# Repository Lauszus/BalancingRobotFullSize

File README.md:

# Balancing robot full size
#### Developed by Kristian Sloth Lauszus and Mads Friis Bornebusch, 2014

The code is released under the GNU General Public License.
_________

This is the code for my full size balancing robot.

Both our paper and poster can be found inside the [Documents](Documents) directory.

Detailed information can be found at the blog post: <http://blog.tkjelectronics.dk/2014/07/full-size-diy-balancing-robot/>.

## Android application

I have also written an Android application for the robot. The source code is available at the following link: <https://github.com/Lauszus/BalancingRobotFullSizeAndroid>.

For more information send me an email at <lauszus@gmail.com>.

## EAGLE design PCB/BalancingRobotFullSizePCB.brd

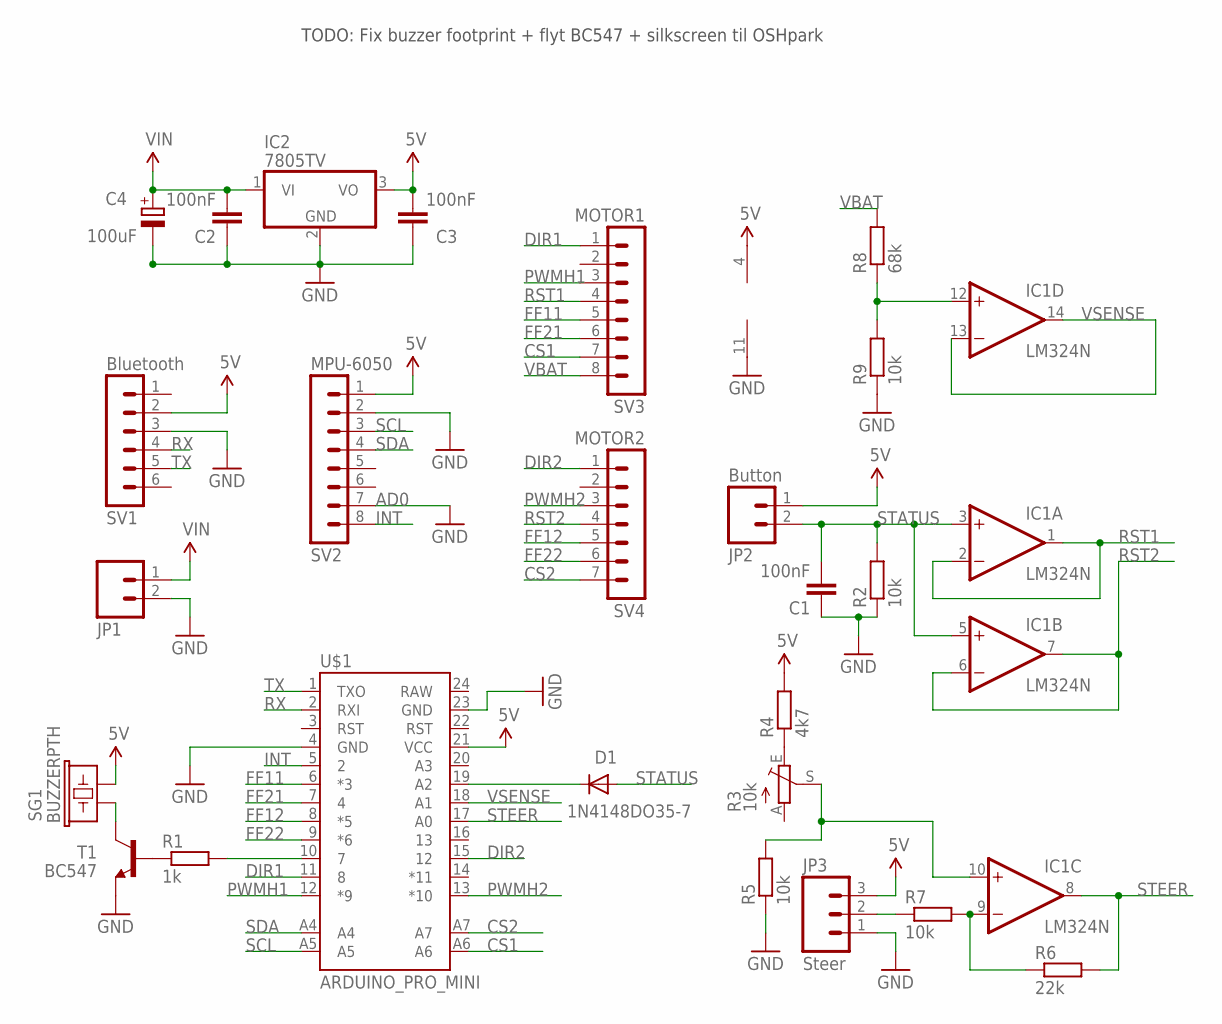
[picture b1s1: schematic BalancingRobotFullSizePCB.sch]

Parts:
C1, C2, C3: 100nF; C025-025X050
C4: 100uF; E2,5-5
D1: 1N4148DO35-7; DO35-7
IC1: LM324N; DIL14
IC2: 7805TV; TO220V
JP1: M02PTH; 1X02
JP2: Button; 1X02
JP3: Steer; 1X03
R1: 1k; 0207/10
R2, R5, R7, R9: 10k; 0207/10
R3: 10k; B25P
R4: 4k7; 0207/10
R6: 22k; 0207/10
R8: 68k; 0207/10
SG1: BUZZERPTH; BUZZER-12MM
SV1: Bluetooth; MA06-1
SV2: MPU-6050; MA08-1
SV3: MOTOR1; MA08-1
SV4: MOTOR2; MA07-1
T1: BC547; TO92
U$1: ARDUINO_PRO_MINI

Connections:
5V: C3.2, IC1.4 (V+), IC2.3 (VO), JP2.1, JP3.3, R4.2, SG1.- (2), SV1.2, SV2.1, U$1.21 (VCC)
CS1: SV3.7, U$1.A6
CS2: SV4.7, U$1.A7
DIR1: SV3.1, U$1.11 (8)
DIR2: SV4.1, U$1.15 (12)
FF11: SV3.5, U$1.6 (*3)
FF12: SV4.5, U$1.8 (*5)
FF21: SV3.6, U$1.7 (4)
FF22: SV4.6, U$1.9 (*6)
GND: C1.1, C2.1, C3.1, C4.-, IC1.11 (V-), IC2.2 (GND), JP1.2, JP3.1, R2.1, R5.1, R9.1, SV1.3, SV2.2, SV2.7, T1.1 (E), U$1.4 (GND), U$1.23 (GND)
INT: SV2.8, U$1.5 (2)
unnamed: IC1.12 (+IN), R8.1, R9.2
unnamed: D1.C, U$1.19 (A2)
unnamed: R1.1, T1.2 (B)
unnamed: SG1.+ (1), T1.3 (C)
unnamed: R1.2, U$1.10 (7)
unnamed: R3.E, R4.1
unnamed: IC1.10 (+IN), R3.S, R5.2
unnamed: IC1.9 (-IN), R6.1, R7.2
unnamed: JP3.2, R7.1
PWMH1: SV3.3, U$1.12 (*9)
PWMH2: SV4.3, U$1.13 (*10)
RST1: IC1.1 (OUT), IC1.2 (-IN), SV3.4
RST2: IC1.6 (-IN), IC1.7 (OUT), SV4.4
RX: SV1.4, U$1.2 (RXI)
SCL: SV2.3, U$1.A5
SDA: SV2.4, U$1.A4
STATUS: C1.2, D1.A, IC1.3 (+IN), IC1.5 (+IN), JP2.2, R2.2
STEER: IC1.8 (OUT), R6.2, U$1.17 (A0)
TX: SV1.5, U$1.1 (TXO)
VBAT: R8.2, SV3.8
VIN: C2.2, C4.+, IC2.1 (VI), JP1.1
VSENSE: IC1.13 (-IN), IC1.14 (OUT), U$1.18 (A1)

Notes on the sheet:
AD0
TODO: Fix buzzer footprint + flyt BC547 + silkscreen til OSHpark

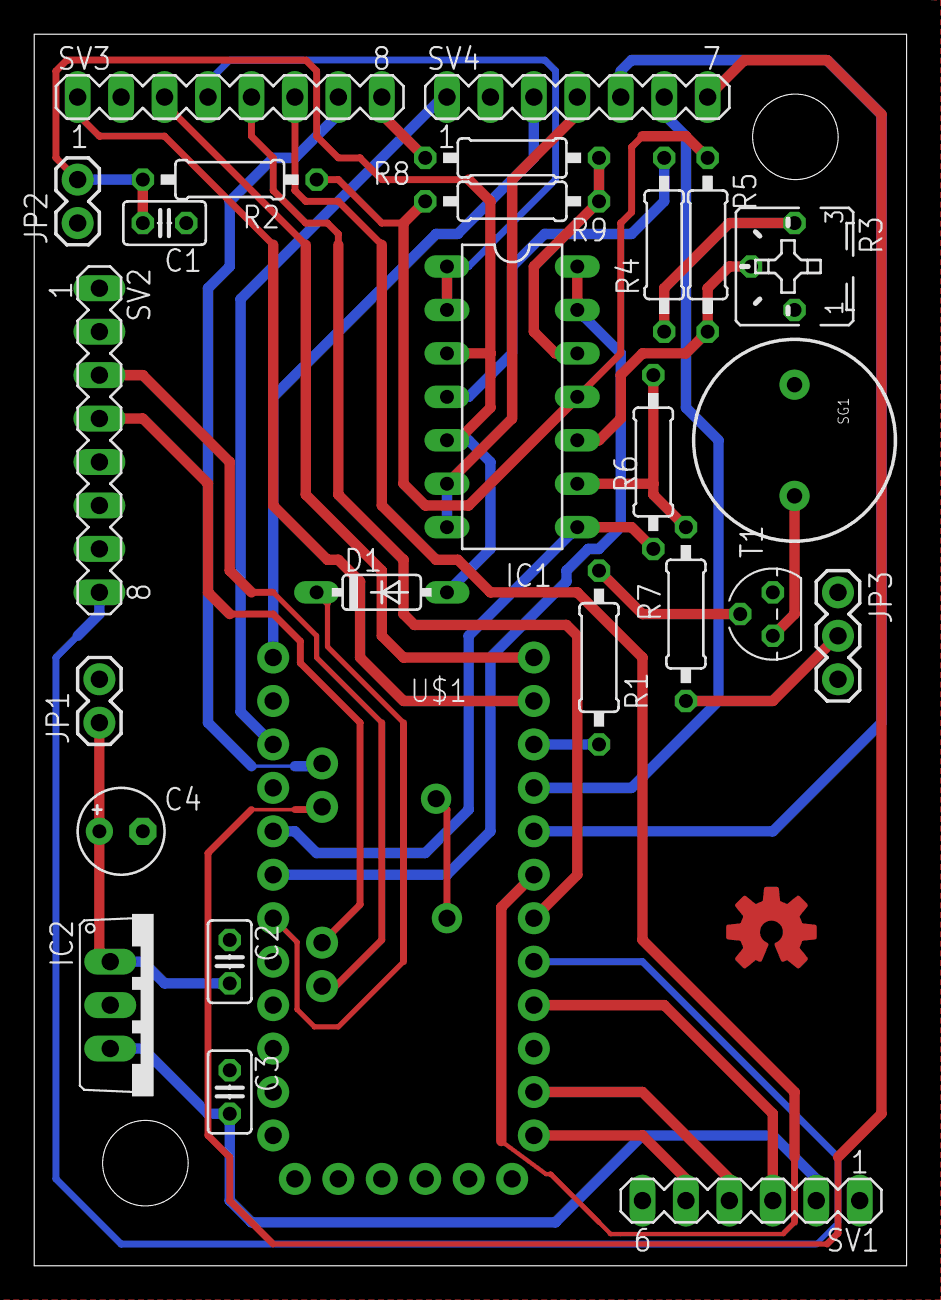
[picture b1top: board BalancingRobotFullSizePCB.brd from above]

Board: 2 copper layers, 51.0 x 72.0 mm, 27 parts (0 on the bottom side), 33 nets.

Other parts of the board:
U$4: OSHWLOGO_TOP_0.2

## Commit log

2014-05-29 First commit
    Still a lot of work to do
2014-05-29 Added license and readme
2014-05-29 Added local copy of avrpins.h
2014-05-29 Removed include trap and added include <avr/io.h>
2014-05-29 Can now compile using Makefile
    Also did some cleanup
2014-05-30 Improved serial protocol
    Still needs a lot of work
2014-05-30 Read deadmanButton. This is used to reset all values.
2014-05-30 Enable turning
2014-05-30 Add short delay until INT is used on the MPU-6050
2014-05-30 Tilt back when speed is increasing
2014-05-31 Only read MPU-6050 when there is actually new data ready
2014-05-31 Set I2C to send stop by default
2014-05-31 Move all pin defined into it's own header
2014-05-31 Decreased I2C_TIMEOUT
    It should never take this long
2014-05-31 Moved stopAndReset function into PID.cpp
2014-05-31 Updated default cfg values and updated some comments
2014-05-31 Updated master Makefile
2014-05-31 Coding style
2014-06-05 Increased I2C_TIMEOUT again
    Also converted from uint16_t to uint8_t
2014-06-05 Swap left and right motor
2014-06-05 Calibrate turning at startup
2014-06-05 Don't constrain iTerm
2014-06-07 Increased turning speed
2014-06-09 Improved serial protocol
2014-06-09 Added Processing app
    Based on the one for Balanduino: https://github.com/TKJElectronics/BalanduinoProcessingApp
2014-06-09 Updated some comments and improved slightly sendData on some devices
2014-06-09 Whitespace
2014-06-10 Can now set and get all values using the Processing application
    Might add some more later on
2014-06-15 Updated some comments and replaced for loop with for each loops in Processing code
2014-06-16 Can now send speed, current draw, turning value, battery level and run time via serial
    Still need to implement current and battery level measurement on a hardware level
2014-06-16 Can now send IMU data
2014-06-17 Measure current draw and battery voltage
2014-06-17 Pin relocation
2014-06-17 Multiply battery level by 100, as the rest of the data
    Also forgot to multiply turningValue by 100
2014-06-18 Define all analog pins in Pins.h
    Also used 68k resistor instead of 47k in voltage divider
2014-06-18 Start the buzzer if the voltage get's to low
    Also check if deadman buttons is pressed before taking current sense measurement
2014-06-18 Only parse incoming serial data if it doesn't update the IMU values
2014-06-18 Make sure that it will never send out info and imu values in the same loop
2014-06-18 Make sure the voltage is also above 5V before starting the buzzer
2014-06-24 Don't divide the current draw
2014-06-24 Deadman button pin location was changed
    Also fixed some comments
2014-06-24 Added PCB
2014-06-24 Uploaded paper and poster
2014-06-25 The IMU was mounted upside down on the final PCB
    Also turning was inverted after we soldered everything together
2014-06-25 Read diagnostic pins - deactivated for now
2014-06-25 Move currentSpeed calculation up before turning
2014-06-29 Update makefile
2014-06-29 Uploaded 3D drawing of motor hub
2014-06-30 Update submodules
2014-07-02 Added link to Android application
2014-07-02 Added image of schematic
2014-07-07 Added link to blog post
2014-07-07 Added readme inside ProcessingApp directory
2014-07-07 Check if NUM_ANALOG_INPUTS is equal to 8
    If not they would need to update the Arduino IDE - see: https://github.com/arduino/Arduino/pull/2148
2014-07-07 Use Wire.setClock to set I2C frequency when using Arduino 1.5.7 or above
    See: https://github.com/arduino/Arduino/pull/1912
2014-07-07 Updated some comments and added static to PWM_FREQUENCY and PWMVALUE
2014-07-07 Move calculation of accAngle inside updateIMUValues() and check if data is ready when calibrating gyro
2014-07-07 The motors are turning opposite, so the other current sense value must be subtracted
2015-03-28 Check that ATmega328P is defined before checking NUM_ANALOG_INPUTS
2015-05-22 New motor driver does not have diagnostic pins
    Link: http://cytron.com.my/p-md30c
2015-05-22 Use second Pro Mini for turning signals
2015-05-23 Updated some comments
2015-05-23 Set LED states back to false if it is not turning
2015-05-23 IMU values can be negative as well
    This didn't affect the Android app, as it converted them to signed values
2015-05-23 Update Kalman filter library
    Needed to update makefile as well, so it is included properly
2015-05-23 Remove unnecessary include
2015-05-23 Simplified the way turning signals are set
2015-05-23 Revert "Set LED states back to false if it is not turning"
    This reverts commit 1fcb2a3cccf8c8604c19d5bcd42bc67a9d6692d6.
2015-05-23 Add some deadband to prevent LEDs from flickering
2015-05-23 Reset both states and the timer, so the LEDs will be off when it starts turning
2015-05-23 Removed duplicated code
2015-05-23 Wait by turning off turn signals to make the transaction look better
2015-05-28 Fixed overflow bug
2015-05-28 Push back a little more when driving
2015-08-23 Updated copyright header
2015-11-08 Renamed directory with 3D model for the motor hub
2015-11-08 Uploaded 3D model of motor driver enclosure
2016-01-07 Make sure that the calculated value in delay is never negative
2016-05-08 Forgot to commit latest lid for the enclosure
2017-10-20 Added link to the Android application on the Google play store
2017-10-20 Added YouTube video thumbnail
2018-02-19 Automatically configure the Bluetooth module the first time it is turned on
2018-03-04 Can now compile the code using PlatformIO
2018-04-30 Only call millis() once in every loop

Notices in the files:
parts and their libraries:
SparkFun-Boards: Licensing: Creative Commons ShareAlike 4.0 International - https://creativecommons.org/licenses/by-sa/4.0
